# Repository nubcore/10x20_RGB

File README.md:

# 10x20_LED_screen
hardware design files and software applications for an esp32c3 + 200 "smart LEDs"  project.

## General

The PCB contains an ESP32-C3, 4 buttons and 200 ws2812B-like "smart LED" components that each contain three 256 level PWM controllers to drive the Red, Green and Blue LED channels. This means that each LED can theoretically display 2^24 colour combinations. The LEDs are supplied with the necessary data using a serial protocol, and are all connected in series in a single "string", so to drive all the LEDs, the ESP32-C3 must send 200 * 24 = 4800 bits of data. The LEDs need this data to be supplied at a net rate of 800,000 bits per second.
The actual low-level protocol used to transmit the data to the LEDs is as follows:

- ALL bits for a string of LEDs must be transmitted as a continuous stream immediately after a "reset pulse"
- A "0"-bit is transmitted as a 4 us high level, followed by an 8 us low level
- A "1"-bit is transmitted as an 8 us high level, followed by a 4 us low level
- After all bits have been transmitted, a 50 us low level serves as a "reset pulse"

This could be done using "bit-banging", but then the ESP can do little else aside. Alternatively, one can put one of the ESP32-C3's hardware peripherals to "alternative use".

## Hardware

The "hardware" folder contains the schematic diagram and KiCAD source files for this project.

__PLEASE NOTE THE FOLLOWING:__

This Do-It-Yourself project comes without any guarantee whatsoever.

5V Power should always be supplied to the LED portion DIRECTLY, NOT via the USB connector on the ESP32-C3 module.

It is, however, possible to supply the ESP32-C3 from the LED portion power supply by fitting a 0 Ohm resistor to R2. R2 should ONLY be fitted if you want to power the ESP32-C3 from the power supply connected to the LED portion, and it is then recommended to completely disconnect the USB cable and remove the USB connector from the ESP32-C3 module to prevent accidentally drawing power for the LED portion through the USB cable connected to the ESP32-C3 module.

Attempting to supply power through the USB connecter to the ESP32-C3 AND the LED portion may lead to damage to the ESP32-C3 module AND/OR to the USB power source. The LED portion alone can draw in excess of 1.5 A, and the ESP32-C3 module PCB traces and components are NOT rated for this. The LED portion does NOT properly negotiate its power draw with the power source by itself, and while the ESP32-C3 might be able to take on this task, there is no guarantee (given that users can run their own code on the ESP32-C3) that it will.

__TL;DR: Do not fit R2 unless you know what you are doing and willing to bear any and all consequences.__

## Software

The "software" folder contains some self-contained example Arduino applications. Two of these applications demonstrate the use of ESP32-C3's hardware peripherals to drive the display
.
### Driving the display with the "RMT" (remote control) perhipheral

The ledscreentest1 example demonstrates the use of the "RMT" perhipheral.Can generate very accurately timed signals, but has enormous memory overhead: it requires 32 times more storage than there is raw data to be sent to the LEDs. 24 bits to be sent to each LED requires 768 bits of memory. Every RGB byte translates to 8 32 bit word accesses. This method uses DMA (Direct memory access) to relieve the processor of these duties: The processor just needs to prepare a block of data and then start the transfer.

### Driving the display with the "SPI" (synchronous serial port) perhipheral 

The ledscreentest2 example demionstrates the use of the "SPI" perhipheral. Signals are less accuratly timed, but do actually work with the types of LEDs tested so far. Overhead is much lower than for the "RMT" method: it requires 4 times more storage than there is raw data to be sent to the LEDs. 24 bits to be sent to each LED requires 96 bits of memory. Moreover, as every (RGB) byte access becomes a single 32 bit word access, processor overhead is relatively limited. This method uses DMA (Direct memory access) to relieve the processor of these duties: The processor just needs to prepare a block of data and then start the transfer.

### "Famous-Falling-Block-Game"-tris

The blocktris example game uses 6 combinations of 2 buttons that are simultaneously pressed to control a falling block:

- start game
- move left
- move right
- turn clockwise
- turn counter-clockwise
- drop

Objective of the game is to score points by completely filling as many rows on the board as possible: 1 row = 1 point, 2 rows = 4 points, 3 rows = 9 points and 4 rows = 16 points. Completed rows are removed from the board, and the game ends when there is no more room for a new piece to spawn.

If you fill in the login credentials of an access point, the module will try to communicate a (global) high-score with a server.

### "Floppy brick"

Fly a brick, avoiding increasingly difficult obstacles along it's path by commanding it to flop using the "flop" button.

## Prerequisites

As Espressif regulary makes breaking changes to their API, it is important that you use the __correct version of the Espressif framework for Arduino: 3.1.3__

After you have installed the Espressif board manager package, you can __select the "ESP32-C3 Dev-module"__, which is compatible with the ESP32-C3 "super-mini" module that is usedin this project.

Please make sure that you have __set the option "USB CDC enable on boot" to "enabled"__ (Arduino tools menu), and that you have selected the correct serial device.

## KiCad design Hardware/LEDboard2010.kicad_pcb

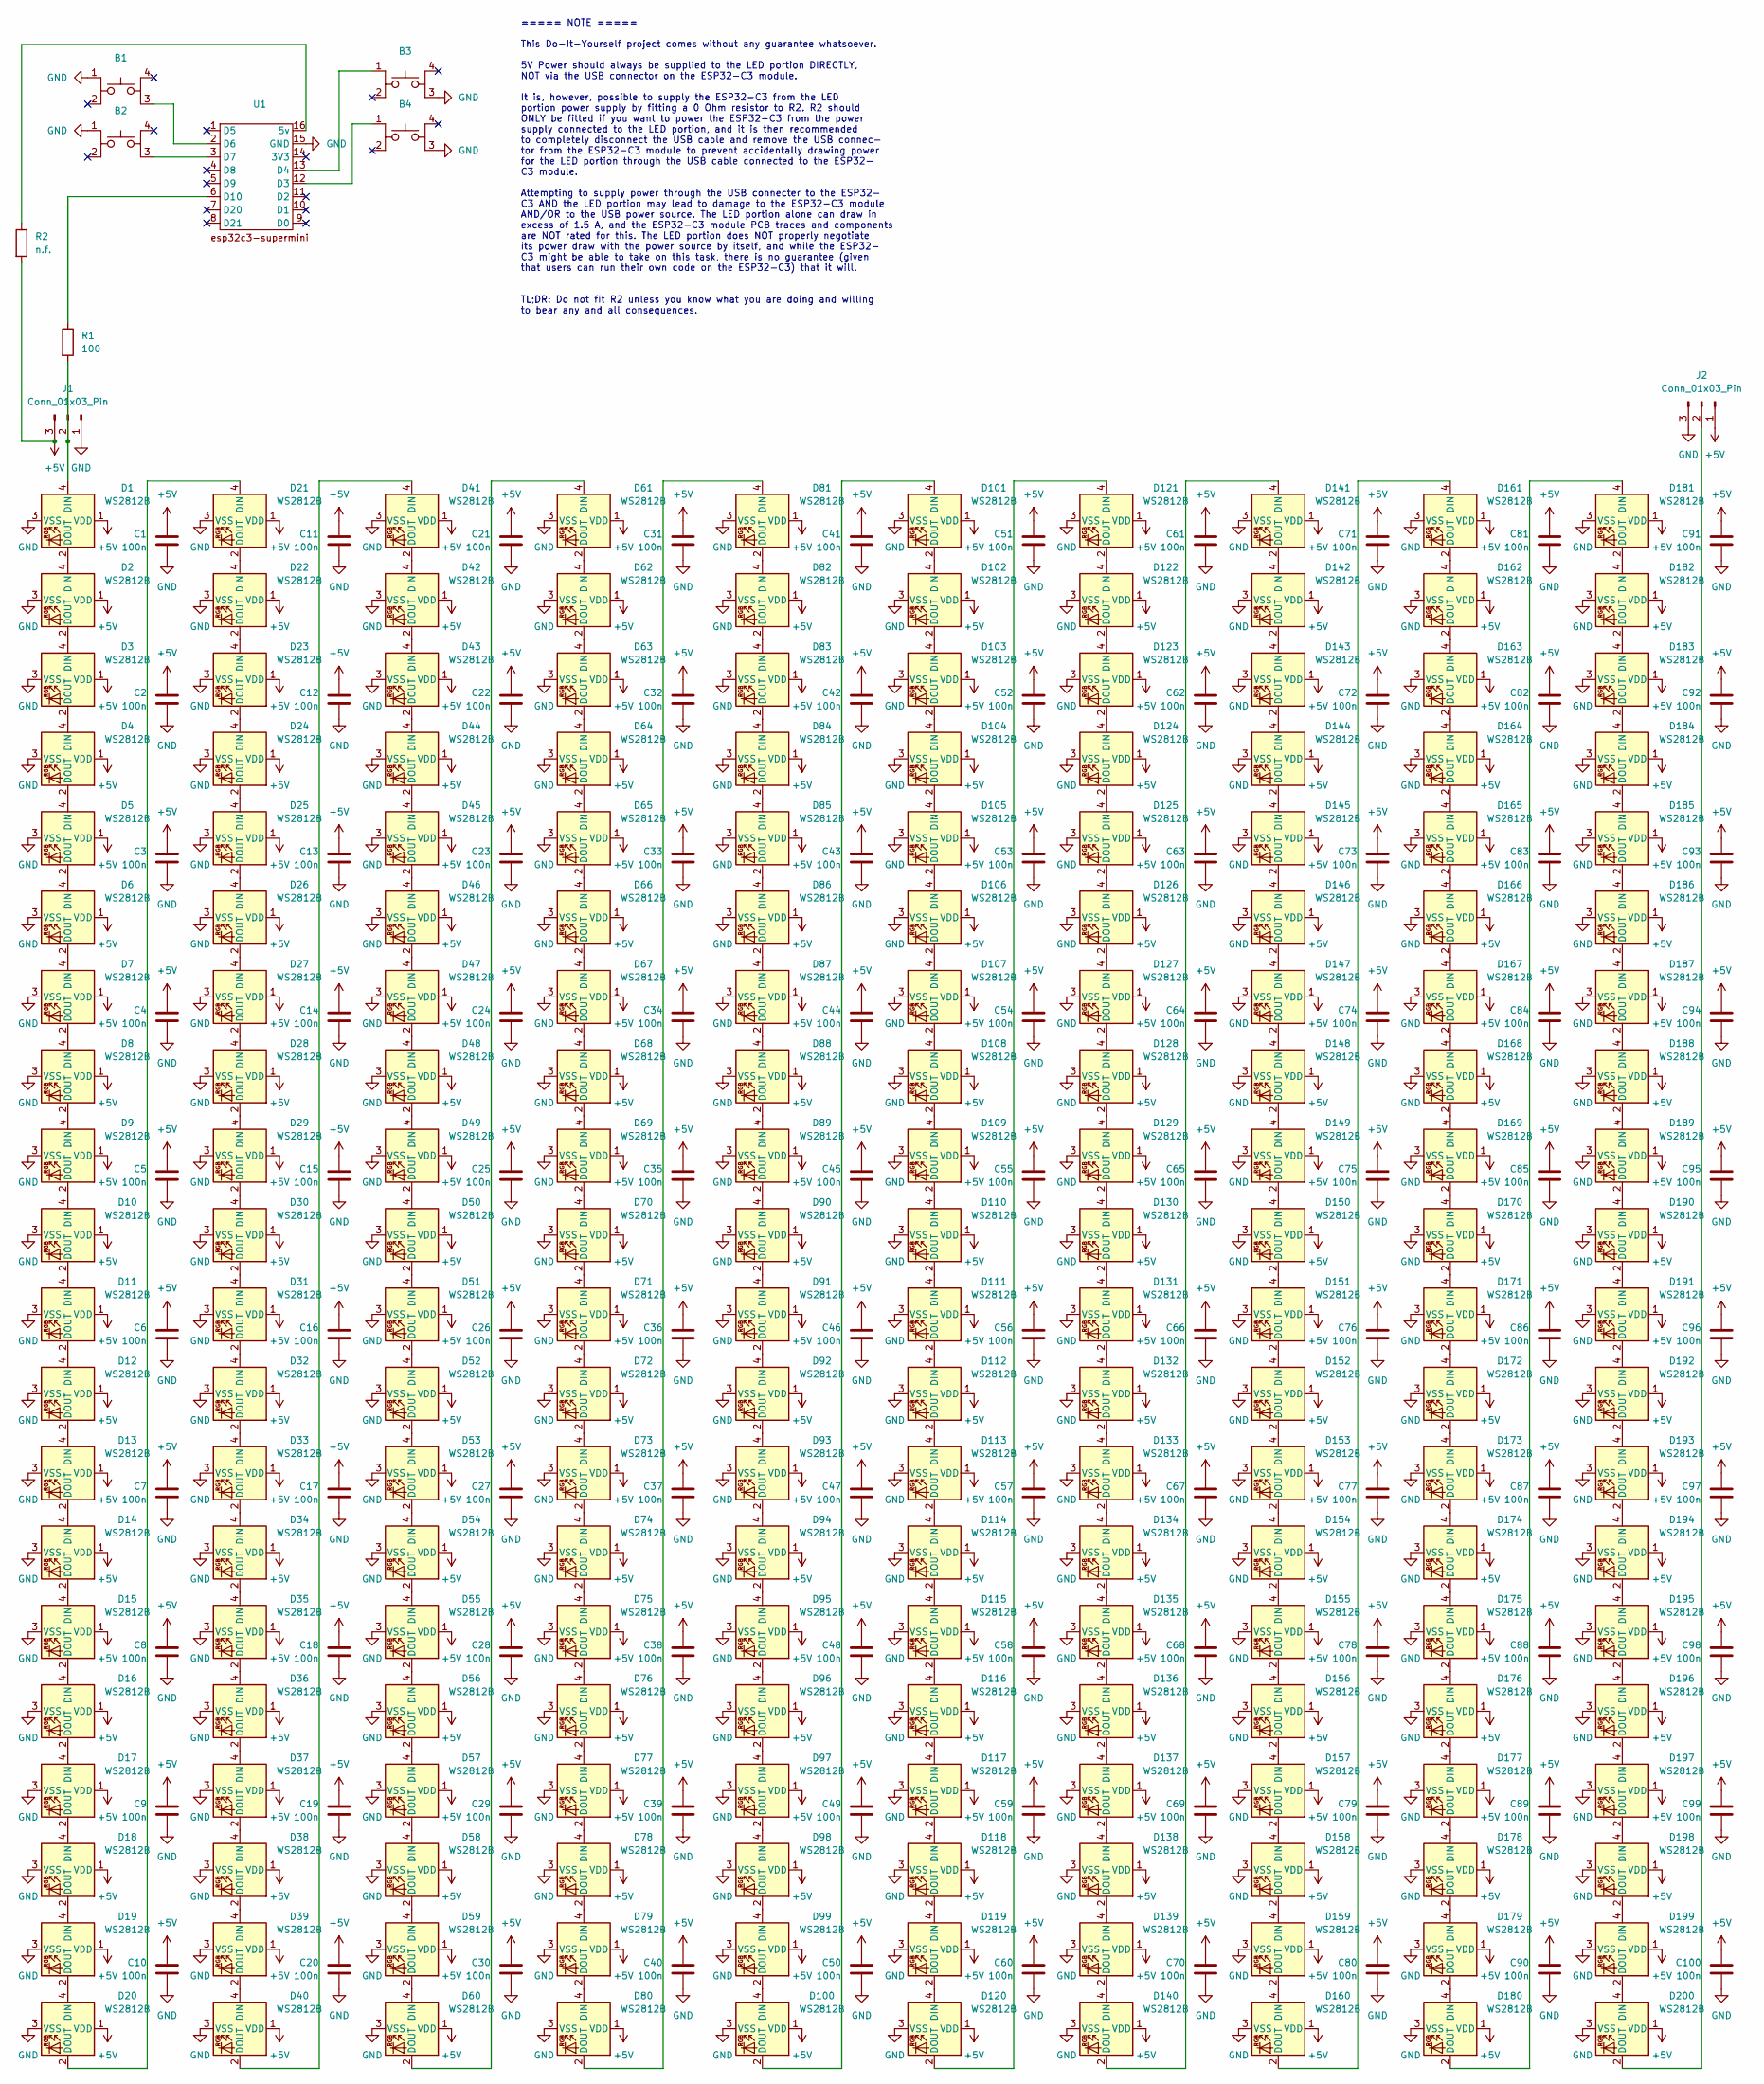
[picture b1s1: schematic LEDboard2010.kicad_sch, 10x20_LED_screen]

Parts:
B1, B2, B3, B4: button
C1, C2, C3, C4, C5, C6, C7, C8, C9, C10, C11, C12, C13, C14, C15, C16, C17, C18, C19, C20, C21, C22, C23, C24, C25, C26, C27, C28, C29, C30, C31, C32, C33, C34, C35, C36, C37, C38, C39, C40, C41, C42, C43, C44, C45, C46, C47, C48, C49, C50, C51, C52, C53, C54, C55, C56, C57, C58, C59, C60, C61, C62, C63, C64, C65, C66, C67, C68, C69, C70, C71, C72, C73, C74, C75, C76, C77, C78, C79, C80, C81, C82, C83, C84, C85, C86, C87, C88, C89, C90, C91, C92, C93, C94, C95, C96, C97, C98, C99, C100: 100n; C_0603
D1, D2, D3, D4, D5, D6, D7, D8, D9, D10, D11, D12, D13, D14, D15, D16, D17, D18, D19, D20, D21, D22, D23, D24, D25, D26, D27, D28, D29, D30, D31, D32, D33, D34, D35, D36, D37, D38, D39, D40, D41, D42, D43, D44, D45, D46, D47, D48, D49, D50, D51, D52, D53, D54, D55, D56, D57, D58, D59, D60, D61, D62, D63, D64, D65, D66, D67, D68, D69, D70, D71, D72, D73, D74, D75, D76, D77, D78, D79, D80, D81, D82, D83, D84, D85, D86, D87, D88, D89, D90, D91, D92, D93, D94, D95, D96, D97, D98, D99, D100, D101, D102, D103, D104, D105, D106, D107, D108, D109, D110, D111, D112, D113, D114, D115, D116, D117, D118, D119, D120, D121, D122, D123, D124, D125, D126, D127, D128, D129, D130, D131, D132, D133, D134, D135, D136, D137, D138, D139, D140, D141, D142, D143, D144, D145, D146, D147, D148, D149, D150, D151, D152, D153, D154, D155, D156, D157, D158, D159, D160, D161, D162, D163, D164, D165, D166, D167, D168, D169, D170, D171, D172, D173, D174, D175, D176, D177, D178, D179, D180, D181, D182, D183, D184, D185, D186, D187, D188, D189, D190, D191, D192, D193, D194, D195, D196, D197, D198, D199, D200: WS2812B; XINGLIGHT XL-0807RGBC-WS2812B-S
J1, J2: Conn_01x03_Pin; datacon
R1: 100; R_0805
R2: n.f.; R_0805
U1: esp32c3

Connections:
+5V: C1.2, C2.2, C3.2, C4.2, C5.2, C6.2, C7.2, C8.2, C9.2, C10.2, C11.2, C12.2, C13.2, C14.2, C15.2, C16.2, C17.2, C18.2, C19.2, C20.2, C21.2, C22.2, C23.2, C24.2, C25.2, C26.2, C27.2, C28.2, C29.2, C30.2, C31.2, C32.2, C33.2, C34.2, C35.2, C36.2, C37.2, C38.2, C39.2, C40.2, C41.2, C42.2, C43.2, C44.2, C45.2, C46.2, C47.2, C48.2, C49.2, C50.2, C51.2, C52.2, C53.2, C54.2, C55.2, C56.2, C57.2, C58.2, C59.2, C60.2, C61.2, C62.2, C63.2, C64.2, C65.2, C66.2, C67.2, C68.2, C69.2, C70.2, C71.2, C72.2, C73.2, C74.2, C75.2, C76.2, C77.2, C78.2, C79.2, C80.2, C81.2, C82.2, C83.2, C84.2, C85.2, C86.2, C87.2, C88.2, C89.2, C90.2, C91.2, C92.2, C93.2, C94.2, C95.2, C96.2, C97.2, C98.2, C99.2, C100.2, D1.1 (VDD), D2.1 (VDD), D3.1 (VDD), D4.1 (VDD), D5.1 (VDD), D6.1 (VDD), D7.1 (VDD), D8.1 (VDD), D9.1 (VDD), D10.1 (VDD), D11.1 (VDD), D12.1 (VDD), D13.1 (VDD), D14.1 (VDD), D15.1 (VDD), D16.1 (VDD), D17.1 (VDD), D18.1 (VDD), D19.1 (VDD), D20.1 (VDD), D21.1 (VDD), D22.1 (VDD), D23.1 (VDD), D24.1 (VDD), D25.1 (VDD), D26.1 (VDD), D27.1 (VDD), D28.1 (VDD), D29.1 (VDD), D30.1 (VDD), D31.1 (VDD), D32.1 (VDD), D33.1 (VDD), D34.1 (VDD), D35.1 (VDD), D36.1 (VDD), D37.1 (VDD), D38.1 (VDD), D39.1 (VDD), D40.1 (VDD), D41.1 (VDD), D42.1 (VDD), D43.1 (VDD), D44.1 (VDD), D45.1 (VDD), D46.1 (VDD), D47.1 (VDD), D48.1 (VDD), D49.1 (VDD), D50.1 (VDD), D51.1 (VDD), D52.1 (VDD), D53.1 (VDD), D54.1 (VDD), D55.1 (VDD), D56.1 (VDD), D57.1 (VDD), D58.1 (VDD), D59.1 (VDD), D60.1 (VDD), D61.1 (VDD), D62.1 (VDD), D63.1 (VDD), D64.1 (VDD), D65.1 (VDD), D66.1 (VDD), D67.1 (VDD), D68.1 (VDD), D69.1 (VDD), D70.1 (VDD), D71.1 (VDD), D72.1 (VDD), D73.1 (VDD), D74.1 (VDD), D75.1 (VDD), D76.1 (VDD), D77.1 (VDD), D78.1 (VDD), D79.1 (VDD), D80.1 (VDD), D81.1 (VDD), D82.1 (VDD), D83.1 (VDD), D84.1 (VDD), D85.1 (VDD), D86.1 (VDD), D87.1 (VDD), D88.1 (VDD), D89.1 (VDD), D90.1 (VDD), D91.1 (VDD), D92.1 (VDD), D93.1 (VDD), D94.1 (VDD), D95.1 (VDD), D96.1 (VDD), D97.1 (VDD), D98.1 (VDD), D99.1 (VDD), D100.1 (VDD), D101.1 (VDD), D102.1 (VDD), D103.1 (VDD), D104.1 (VDD), D105.1 (VDD), D106.1 (VDD), D107.1 (VDD), D108.1 (VDD), D109.1 (VDD), D110.1 (VDD), D111.1 (VDD), D112.1 (VDD), D113.1 (VDD), D114.1 (VDD), D115.1 (VDD), D116.1 (VDD), D117.1 (VDD), D118.1 (VDD), D119.1 (VDD), D120.1 (VDD), D121.1 (VDD), D122.1 (VDD), D123.1 (VDD), D124.1 (VDD), D125.1 (VDD), D126.1 (VDD), D127.1 (VDD), D128.1 (VDD), D129.1 (VDD), D130.1 (VDD), D131.1 (VDD), D132.1 (VDD), D133.1 (VDD), D134.1 (VDD), D135.1 (VDD), D136.1 (VDD), D137.1 (VDD), D138.1 (VDD), D139.1 (VDD), D140.1 (VDD), D141.1 (VDD), D142.1 (VDD), D143.1 (VDD), D144.1 (VDD), D145.1 (VDD), D146.1 (VDD), D147.1 (VDD), D148.1 (VDD), D149.1 (VDD), D150.1 (VDD), D151.1 (VDD), D152.1 (VDD), D153.1 (VDD), D154.1 (VDD), D155.1 (VDD), D156.1 (VDD), D157.1 (VDD), D158.1 (VDD), D159.1 (VDD), D160.1 (VDD), D161.1 (VDD), D162.1 (VDD), D163.1 (VDD), D164.1 (VDD), D165.1 (VDD), D166.1 (VDD), D167.1 (VDD), D168.1 (VDD), D169.1 (VDD), D170.1 (VDD), D171.1 (VDD), D172.1 (VDD), D173.1 (VDD), D174.1 (VDD), D175.1 (VDD), D176.1 (VDD), D177.1 (VDD), D178.1 (VDD), D179.1 (VDD), D180.1 (VDD), D181.1 (VDD), D182.1 (VDD), D183.1 (VDD), D184.1 (VDD), D185.1 (VDD), D186.1 (VDD), D187.1 (VDD), D188.1 (VDD), D189.1 (VDD), D190.1 (VDD), D191.1 (VDD), D192.1 (VDD), D193.1 (VDD), D194.1 (VDD), D195.1 (VDD), D196.1 (VDD), D197.1 (VDD), D198.1 (VDD), D199.1 (VDD), D200.1 (VDD), J1.3, J2.1, R2.2
GND: B1.1, B2.1, B3.3, B4.3, C1.1, C2.1, C3.1, C4.1, C5.1, C6.1, C7.1, C8.1, C9.1, C10.1, C11.1, C12.1, C13.1, C14.1, C15.1, C16.1, C17.1, C18.1, C19.1, C20.1, C21.1, C22.1, C23.1, C24.1, C25.1, C26.1, C27.1, C28.1, C29.1, C30.1, C31.1, C32.1, C33.1, C34.1, C35.1, C36.1, C37.1, C38.1, C39.1, C40.1, C41.1, C42.1, C43.1, C44.1, C45.1, C46.1, C47.1, C48.1, C49.1, C50.1, C51.1, C52.1, C53.1, C54.1, C55.1, C56.1, C57.1, C58.1, C59.1, C60.1, C61.1, C62.1, C63.1, C64.1, C65.1, C66.1, C67.1, C68.1, C69.1, C70.1, C71.1, C72.1, C73.1, C74.1, C75.1, C76.1, C77.1, C78.1, C79.1, C80.1, C81.1, C82.1, C83.1, C84.1, C85.1, C86.1, C87.1, C88.1, C89.1, C90.1, C91.1, C92.1, C93.1, C94.1, C95.1, C96.1, C97.1, C98.1, C99.1, C100.1, D1.3 (VSS), D2.3 (VSS), D3.3 (VSS), D4.3 (VSS), D5.3 (VSS), D6.3 (VSS), D7.3 (VSS), D8.3 (VSS), D9.3 (VSS), D10.3 (VSS), D11.3 (VSS), D12.3 (VSS), D13.3 (VSS), D14.3 (VSS), D15.3 (VSS), D16.3 (VSS), D17.3 (VSS), D18.3 (VSS), D19.3 (VSS), D20.3 (VSS), D21.3 (VSS), D22.3 (VSS), D23.3 (VSS), D24.3 (VSS), D25.3 (VSS), D26.3 (VSS), D27.3 (VSS), D28.3 (VSS), D29.3 (VSS), D30.3 (VSS), D31.3 (VSS), D32.3 (VSS), D33.3 (VSS), D34.3 (VSS), D35.3 (VSS), D36.3 (VSS), D37.3 (VSS), D38.3 (VSS), D39.3 (VSS), D40.3 (VSS), D41.3 (VSS), D42.3 (VSS), D43.3 (VSS), D44.3 (VSS), D45.3 (VSS), D46.3 (VSS), D47.3 (VSS), D48.3 (VSS), D49.3 (VSS), D50.3 (VSS), D51.3 (VSS), D52.3 (VSS), D53.3 (VSS), D54.3 (VSS), D55.3 (VSS), D56.3 (VSS), D57.3 (VSS), D58.3 (VSS), D59.3 (VSS), D60.3 (VSS), D61.3 (VSS), D62.3 (VSS), D63.3 (VSS), D64.3 (VSS), D65.3 (VSS), D66.3 (VSS), D67.3 (VSS), D68.3 (VSS), D69.3 (VSS), D70.3 (VSS), D71.3 (VSS), D72.3 (VSS), D73.3 (VSS), D74.3 (VSS), D75.3 (VSS), D76.3 (VSS), D77.3 (VSS), D78.3 (VSS), D79.3 (VSS), D80.3 (VSS), D81.3 (VSS), D82.3 (VSS), D83.3 (VSS), D84.3 (VSS), D85.3 (VSS), D86.3 (VSS), D87.3 (VSS), D88.3 (VSS), D89.3 (VSS), D90.3 (VSS), D91.3 (VSS), D92.3 (VSS), D93.3 (VSS), D94.3 (VSS), D95.3 (VSS), D96.3 (VSS), D97.3 (VSS), D98.3 (VSS), D99.3 (VSS), D100.3 (VSS), D101.3 (VSS), D102.3 (VSS), D103.3 (VSS), D104.3 (VSS), D105.3 (VSS), D106.3 (VSS), D107.3 (VSS), D108.3 (VSS), D109.3 (VSS), D110.3 (VSS), D111.3 (VSS), D112.3 (VSS), D113.3 (VSS), D114.3 (VSS), D115.3 (VSS), D116.3 (VSS), D117.3 (VSS), D118.3 (VSS), D119.3 (VSS), D120.3 (VSS), D121.3 (VSS), D122.3 (VSS), D123.3 (VSS), D124.3 (VSS), D125.3 (VSS), D126.3 (VSS), D127.3 (VSS), D128.3 (VSS), D129.3 (VSS), D130.3 (VSS), D131.3 (VSS), D132.3 (VSS), D133.3 (VSS), D134.3 (VSS), D135.3 (VSS), D136.3 (VSS), D137.3 (VSS), D138.3 (VSS), D139.3 (VSS), D140.3 (VSS), D141.3 (VSS), D142.3 (VSS), D143.3 (VSS), D144.3 (VSS), D145.3 (VSS), D146.3 (VSS), D147.3 (VSS), D148.3 (VSS), D149.3 (VSS), D150.3 (VSS), D151.3 (VSS), D152.3 (VSS), D153.3 (VSS), D154.3 (VSS), D155.3 (VSS), D156.3 (VSS), D157.3 (VSS), D158.3 (VSS), D159.3 (VSS), D160.3 (VSS), D161.3 (VSS), D162.3 (VSS), D163.3 (VSS), D164.3 (VSS), D165.3 (VSS), D166.3 (VSS), D167.3 (VSS), D168.3 (VSS), D169.3 (VSS), D170.3 (VSS), D171.3 (VSS), D172.3 (VSS), D173.3 (VSS), D174.3 (VSS), D175.3 (VSS), D176.3 (VSS), D177.3 (VSS), D178.3 (VSS), D179.3 (VSS), D180.3 (VSS), D181.3 (VSS), D182.3 (VSS), D183.3 (VSS), D184.3 (VSS), D185.3 (VSS), D186.3 (VSS), D187.3 (VSS), D188.3 (VSS), D189.3 (VSS), D190.3 (VSS), D191.3 (VSS), D192.3 (VSS), D193.3 (VSS), D194.3 (VSS), D195.3 (VSS), D196.3 (VSS), D197.3 (VSS), D198.3 (VSS), D199.3 (VSS), D200.3 (VSS), J1.1, J2.3, U1.15 (GND)
unnamed: D1.4 (DIN), J1.2, R1.2
unnamed: D1.2 (DOUT), D2.4 (DIN)
unnamed: D2.2 (DOUT), D3.4 (DIN)
unnamed: D3.2 (DOUT), D4.4 (DIN)
unnamed: D4.2 (DOUT), D5.4 (DIN)
unnamed: D5.2 (DOUT), D6.4 (DIN)
unnamed: D6.2 (DOUT), D7.4 (DIN)
unnamed: D7.2 (DOUT), D8.4 (DIN)
unnamed: D8.2 (DOUT), D9.4 (DIN)
unnamed: D9.2 (DOUT), D10.4 (DIN)
unnamed: D10.2 (DOUT), D11.4 (DIN)
unnamed: D11.2 (DOUT), D12.4 (DIN)
unnamed: D12.2 (DOUT), D13.4 (DIN)
unnamed: D13.2 (DOUT), D14.4 (DIN)
unnamed: D14.2 (DOUT), D15.4 (DIN)
unnamed: D15.2 (DOUT), D16.4 (DIN)
unnamed: D16.2 (DOUT), D17.4 (DIN)
unnamed: D17.2 (DOUT), D18.4 (DIN)
unnamed: D18.2 (DOUT), D19.4 (DIN)
unnamed: D19.2 (DOUT), D20.4 (DIN)
unnamed: D20.2 (DOUT), D21.4 (DIN)
unnamed: D21.2 (DOUT), D22.4 (DIN)
unnamed: D22.2 (DOUT), D23.4 (DIN)
unnamed: D23.2 (DOUT), D24.4 (DIN)
unnamed: D24.2 (DOUT), D25.4 (DIN)
unnamed: D25.2 (DOUT), D26.4 (DIN)
unnamed: D26.2 (DOUT), D27.4 (DIN)
unnamed: D27.2 (DOUT), D28.4 (DIN)
unnamed: D28.2 (DOUT), D29.4 (DIN)
unnamed: D29.2 (DOUT), D30.4 (DIN)
unnamed: D30.2 (DOUT), D31.4 (DIN)
unnamed: D31.2 (DOUT), D32.4 (DIN)
unnamed: D32.2 (DOUT), D33.4 (DIN)
unnamed: D33.2 (DOUT), D34.4 (DIN)
unnamed: D34.2 (DOUT), D35.4 (DIN)
unnamed: D35.2 (DOUT), D36.4 (DIN)
unnamed: D36.2 (DOUT), D37.4 (DIN)
unnamed: D37.2 (DOUT), D38.4 (DIN)
unnamed: D38.2 (DOUT), D39.4 (DIN)
unnamed: D39.2 (DOUT), D40.4 (DIN)
unnamed: D40.2 (DOUT), D41.4 (DIN)
unnamed: D41.2 (DOUT), D42.4 (DIN)
unnamed: D42.2 (DOUT), D43.4 (DIN)
unnamed: D43.2 (DOUT), D44.4 (DIN)
unnamed: D44.2 (DOUT), D45.4 (DIN)
unnamed: D45.2 (DOUT), D46.4 (DIN)
unnamed: D46.2 (DOUT), D47.4 (DIN)
unnamed: D47.2 (DOUT), D48.4 (DIN)
unnamed: D48.2 (DOUT), D49.4 (DIN)
unnamed: D49.2 (DOUT), D50.4 (DIN)
unnamed: D50.2 (DOUT), D51.4 (DIN)
unnamed: D51.2 (DOUT), D52.4 (DIN)
unnamed: D52.2 (DOUT), D53.4 (DIN)
unnamed: D53.2 (DOUT), D54.4 (DIN)
unnamed: D54.2 (DOUT), D55.4 (DIN)
unnamed: D55.2 (DOUT), D56.4 (DIN)
unnamed: D56.2 (DOUT), D57.4 (DIN)
unnamed: D57.2 (DOUT), D58.4 (DIN)
unnamed: D58.2 (DOUT), D59.4 (DIN)
unnamed: D59.2 (DOUT), D60.4 (DIN)
unnamed: D60.2 (DOUT), D61.4 (DIN)
unnamed: D61.2 (DOUT), D62.4 (DIN)
unnamed: D62.2 (DOUT), D63.4 (DIN)
unnamed: D63.2 (DOUT), D64.4 (DIN)
unnamed: D64.2 (DOUT), D65.4 (DIN)
unnamed: D65.2 (DOUT), D66.4 (DIN)
unnamed: D66.2 (DOUT), D67.4 (DIN)
unnamed: D67.2 (DOUT), D68.4 (DIN)
unnamed: D68.2 (DOUT), D69.4 (DIN)
unnamed: D69.2 (DOUT), D70.4 (DIN)
unnamed: D70.2 (DOUT), D71.4 (DIN)
unnamed: D71.2 (DOUT), D72.4 (DIN)
unnamed: D72.2 (DOUT), D73.4 (DIN)
unnamed: D73.2 (DOUT), D74.4 (DIN)
unnamed: D74.2 (DOUT), D75.4 (DIN)
unnamed: D75.2 (DOUT), D76.4 (DIN)
unnamed: D76.2 (DOUT), D77.4 (DIN)
unnamed: D77.2 (DOUT), D78.4 (DIN)
unnamed: D78.2 (DOUT), D79.4 (DIN)
unnamed: D79.2 (DOUT), D80.4 (DIN)
unnamed: D80.2 (DOUT), D81.4 (DIN)
unnamed: D81.2 (DOUT), D82.4 (DIN)
unnamed: D82.2 (DOUT), D83.4 (DIN)
unnamed: D83.2 (DOUT), D84.4 (DIN)
unnamed: D84.2 (DOUT), D85.4 (DIN)
unnamed: D85.2 (DOUT), D86.4 (DIN)
unnamed: D86.2 (DOUT), D87.4 (DIN)
unnamed: D87.2 (DOUT), D88.4 (DIN)
unnamed: D88.2 (DOUT), D89.4 (DIN)
unnamed: D89.2 (DOUT), D90.4 (DIN)
unnamed: D90.2 (DOUT), D91.4 (DIN)
unnamed: D91.2 (DOUT), D92.4 (DIN)
unnamed: D92.2 (DOUT), D93.4 (DIN)
unnamed: D93.2 (DOUT), D94.4 (DIN)
unnamed: D94.2 (DOUT), D95.4 (DIN)
unnamed: D95.2 (DOUT), D96.4 (DIN)
unnamed: D96.2 (DOUT), D97.4 (DIN)
unnamed: D97.2 (DOUT), D98.4 (DIN)
unnamed: D98.2 (DOUT), D99.4 (DIN)
unnamed: D99.2 (DOUT), D100.4 (DIN)
unnamed: D100.2 (DOUT), D101.4 (DIN)
unnamed: D101.2 (DOUT), D102.4 (DIN)
unnamed: D102.2 (DOUT), D103.4 (DIN)
unnamed: D103.2 (DOUT), D104.4 (DIN)
unnamed: D104.2 (DOUT), D105.4 (DIN)
unnamed: D105.2 (DOUT), D106.4 (DIN)
unnamed: D106.2 (DOUT), D107.4 (DIN)
unnamed: D107.2 (DOUT), D108.4 (DIN)
unnamed: D108.2 (DOUT), D109.4 (DIN)
unnamed: D109.2 (DOUT), D110.4 (DIN)
unnamed: D110.2 (DOUT), D111.4 (DIN)
unnamed: D111.2 (DOUT), D112.4 (DIN)
unnamed: D112.2 (DOUT), D113.4 (DIN)
unnamed: D113.2 (DOUT), D114.4 (DIN)
unnamed: D114.2 (DOUT), D115.4 (DIN)
unnamed: D115.2 (DOUT), D116.4 (DIN)
unnamed: D116.2 (DOUT), D117.4 (DIN)
unnamed: D117.2 (DOUT), D118.4 (DIN)
unnamed: D118.2 (DOUT), D119.4 (DIN)
unnamed: D119.2 (DOUT), D120.4 (DIN)
unnamed: D120.2 (DOUT), D121.4 (DIN)
unnamed: D121.2 (DOUT), D122.4 (DIN)
unnamed: D122.2 (DOUT), D123.4 (DIN)
unnamed: D123.2 (DOUT), D124.4 (DIN)
unnamed: D124.2 (DOUT), D125.4 (DIN)
unnamed: D125.2 (DOUT), D126.4 (DIN)
unnamed: D126.2 (DOUT), D127.4 (DIN)
unnamed: D127.2 (DOUT), D128.4 (DIN)
unnamed: D128.2 (DOUT), D129.4 (DIN)
unnamed: D129.2 (DOUT), D130.4 (DIN)
unnamed: D130.2 (DOUT), D131.4 (DIN)
unnamed: D131.2 (DOUT), D132.4 (DIN)
unnamed: D132.2 (DOUT), D133.4 (DIN)
unnamed: D133.2 (DOUT), D134.4 (DIN)
unnamed: D134.2 (DOUT), D135.4 (DIN)
unnamed: D135.2 (DOUT), D136.4 (DIN)
unnamed: D136.2 (DOUT), D137.4 (DIN)
unnamed: D137.2 (DOUT), D138.4 (DIN)
unnamed: D138.2 (DOUT), D139.4 (DIN)
unnamed: D139.2 (DOUT), D140.4 (DIN)
unnamed: D140.2 (DOUT), D141.4 (DIN)
unnamed: D141.2 (DOUT), D142.4 (DIN)
unnamed: D142.2 (DOUT), D143.4 (DIN)
unnamed: D143.2 (DOUT), D144.4 (DIN)
unnamed: D144.2 (DOUT), D145.4 (DIN)
unnamed: D145.2 (DOUT), D146.4 (DIN)
unnamed: D146.2 (DOUT), D147.4 (DIN)
unnamed: D147.2 (DOUT), D148.4 (DIN)
unnamed: D148.2 (DOUT), D149.4 (DIN)
unnamed: D149.2 (DOUT), D150.4 (DIN)
unnamed: D150.2 (DOUT), D151.4 (DIN)
unnamed: D151.2 (DOUT), D152.4 (DIN)
unnamed: D152.2 (DOUT), D153.4 (DIN)
unnamed: D153.2 (DOUT), D154.4 (DIN)
unnamed: D154.2 (DOUT), D155.4 (DIN)
unnamed: D155.2 (DOUT), D156.4 (DIN)
unnamed: D156.2 (DOUT), D157.4 (DIN)
unnamed: D157.2 (DOUT), D158.4 (DIN)
unnamed: D158.2 (DOUT), D159.4 (DIN)
unnamed: D159.2 (DOUT), D160.4 (DIN)
unnamed: D160.2 (DOUT), D161.4 (DIN)
unnamed: D161.2 (DOUT), D162.4 (DIN)
unnamed: D162.2 (DOUT), D163.4 (DIN)
unnamed: D163.2 (DOUT), D164.4 (DIN)
unnamed: D164.2 (DOUT), D165.4 (DIN)
unnamed: D165.2 (DOUT), D166.4 (DIN)
unnamed: D166.2 (DOUT), D167.4 (DIN)
unnamed: D167.2 (DOUT), D168.4 (DIN)
unnamed: D168.2 (DOUT), D169.4 (DIN)
unnamed: D169.2 (DOUT), D170.4 (DIN)
unnamed: D170.2 (DOUT), D171.4 (DIN)
unnamed: D171.2 (DOUT), D172.4 (DIN)
unnamed: D172.2 (DOUT), D173.4 (DIN)
unnamed: D173.2 (DOUT), D174.4 (DIN)
unnamed: D174.2 (DOUT), D175.4 (DIN)
unnamed: D175.2 (DOUT), D176.4 (DIN)
unnamed: D176.2 (DOUT), D177.4 (DIN)
unnamed: D177.2 (DOUT), D178.4 (DIN)
unnamed: D178.2 (DOUT), D179.4 (DIN)
unnamed: D179.2 (DOUT), D180.4 (DIN)
unnamed: D180.2 (DOUT), D181.4 (DIN)
unnamed: D181.2 (DOUT), D182.4 (DIN)
unnamed: D182.2 (DOUT), D183.4 (DIN)
unnamed: D183.2 (DOUT), D184.4 (DIN)
unnamed: D184.2 (DOUT), D185.4 (DIN)
unnamed: D185.2 (DOUT), D186.4 (DIN)
unnamed: D186.2 (DOUT), D187.4 (DIN)
unnamed: D187.2 (DOUT), D188.4 (DIN)
unnamed: D188.2 (DOUT), D189.4 (DIN)
unnamed: D189.2 (DOUT), D190.4 (DIN)
unnamed: D190.2 (DOUT), D191.4 (DIN)
unnamed: D191.2 (DOUT), D192.4 (DIN)
unnamed: D192.2 (DOUT), D193.4 (DIN)
unnamed: D193.2 (DOUT), D194.4 (DIN)
unnamed: D194.2 (DOUT), D195.4 (DIN)
unnamed: D195.2 (DOUT), D196.4 (DIN)
unnamed: D196.2 (DOUT), D197.4 (DIN)
unnamed: D197.2 (DOUT), D198.4 (DIN)
unnamed: D198.2 (DOUT), D199.4 (DIN)
unnamed: D199.2 (DOUT), D200.4 (DIN)
unnamed: D200.2 (DOUT), J2.2
unnamed: R2.1, U1.16 (5v)
unnamed: B4.1, U1.12 (D3)
unnamed: B3.1, U1.13 (D4)
unnamed: B1.3, U1.2 (D6)
unnamed: B2.3, U1.3 (D7)
unnamed: R1.1, U1.6 (D10)

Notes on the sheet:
===== NOTE ===== This Do-It-Yourself project comes without any guarantee whatsoever. 5V Power should always be supplied to the LED portion DIRECTLY, NOT via the USB connector on the ESP32-C3 module. It is, however, possible to supply the ESP32-C3 from the LED portion power supply by fitting a 0 Ohm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

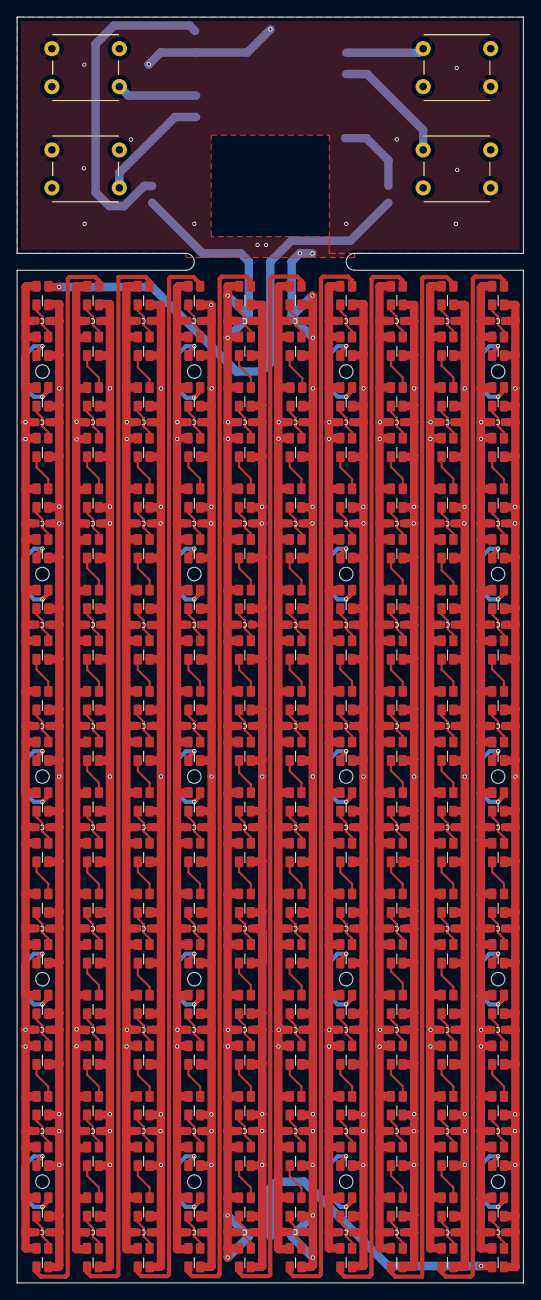
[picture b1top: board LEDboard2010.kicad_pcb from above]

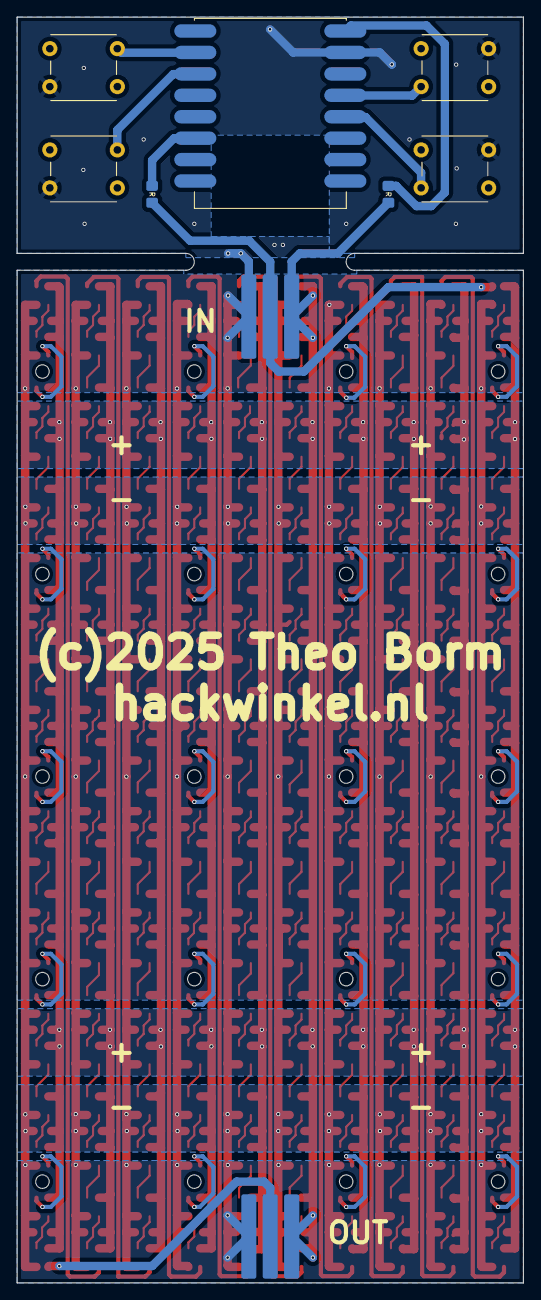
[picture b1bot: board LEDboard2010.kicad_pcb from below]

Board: 2 copper layers, 60.0 x 150.0 mm, 309 parts (5 on the bottom side), 209 nets.

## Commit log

2025-08-17 MyTest
2025-08-17 updated cyckel to 1 Hz vert

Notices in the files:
Hardware/LEDboard2010.kicad_pcb:
(c)2025 Theo Borm
